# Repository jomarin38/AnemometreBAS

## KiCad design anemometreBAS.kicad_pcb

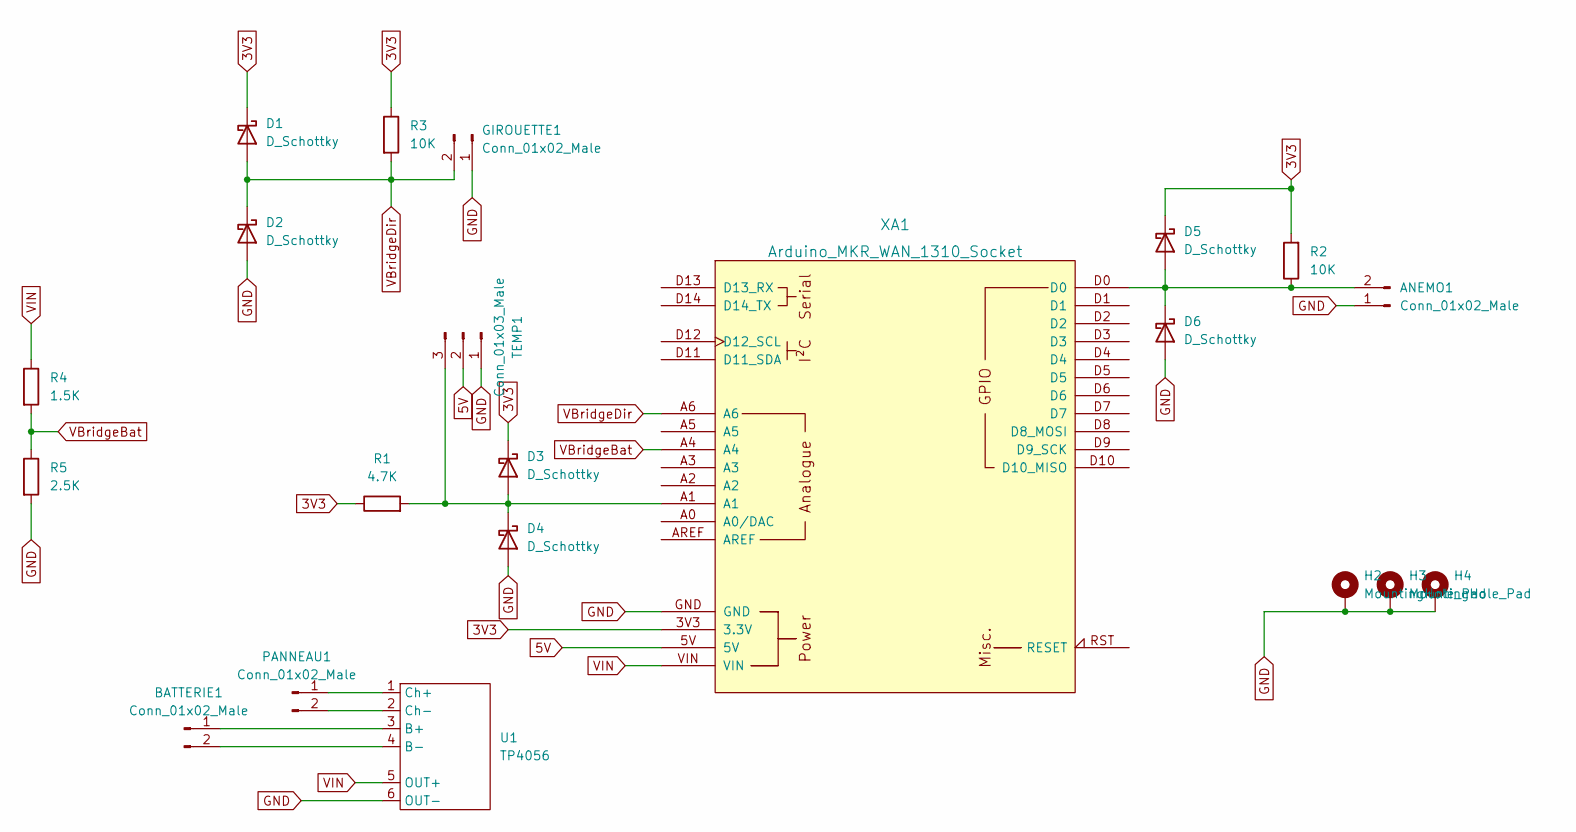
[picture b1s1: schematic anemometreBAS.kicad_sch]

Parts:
ANEMO1: Conn_01x02_Male; JST_XH_B3B-XH-A_1x03_P2.50mm_Vertical
BATTERIE1: Conn_01x02_Male; JST_XH_B2B-XH-A_1x02_P2.50mm_Vertical
D1, D2, D3, D4, D5, D6: D_Schottky; D_DO-35_SOD27_P7.62mm_Horizontal
GIROUETTE1: Conn_01x02_Male; JST_XH_B3B-XH-A_1x03_P2.50mm_Vertical
H2, H3, H4: MountingHole_Pad; MountingHole_3.2mm_M3_Pad_TopBottom
PANNEAU1: Conn_01x02_Male; JST_XH_B2B-XH-A_1x02_P2.50mm_Vertical
R1: 4.7K; R_Axial_DIN0204_L3.6mm_D1.6mm_P7.62mm_Horizontal
R2, R3: 10K; R_Axial_DIN0204_L3.6mm_D1.6mm_P7.62mm_Horizontal
R4: 1.5K; R_Axial_DIN0204_L3.6mm_D1.6mm_P7.62mm_Horizontal
R5: 2.5K; R_Axial_DIN0204_L3.6mm_D1.6mm_P7.62mm_Horizontal
TEMP1: Conn_01x03_Male; JST_XH_B3B-XH-A_1x03_P2.50mm_Vertical
U1: TP4056
XA1: Arduino_MKR_WAN_1310_Socket; Arduino_MKR_FOX_1200_Socket

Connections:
3V3: D1.1 (K), D3.1 (K), D5.1 (K), R1.1, R2.2, R3.1, XA1.3V3 (3.3V)
5V: TEMP1.2, XA1.5V
GND: ANEMO1.1, D2.2 (A), D4.2 (A), D6.2 (A), GIROUETTE1.1, H2.1, H3.1, H4.1, R5.2, TEMP1.1, U1.6 (OUT-), XA1.GND
unnamed: BATTERIE1.1, U1.3 (B+)
unnamed: BATTERIE1.2, U1.4 (B-)
unnamed: PANNEAU1.1, U1.1 (Ch+)
unnamed: PANNEAU1.2, U1.2 (Ch-)
unnamed: D3.2 (A), D4.1 (K), R1.2, TEMP1.3, XA1.A1
unnamed: ANEMO1.2, D5.2 (A), D6.1 (K), R2.1, XA1.D0
VBridgeBat: R4.2, R5.1, XA1.A4
VBridgeDir: D1.2 (A), D2.1 (K), GIROUETTE1.2, R3.2, XA1.A6
VIN: R4.1, U1.5 (OUT+), XA1.VIN

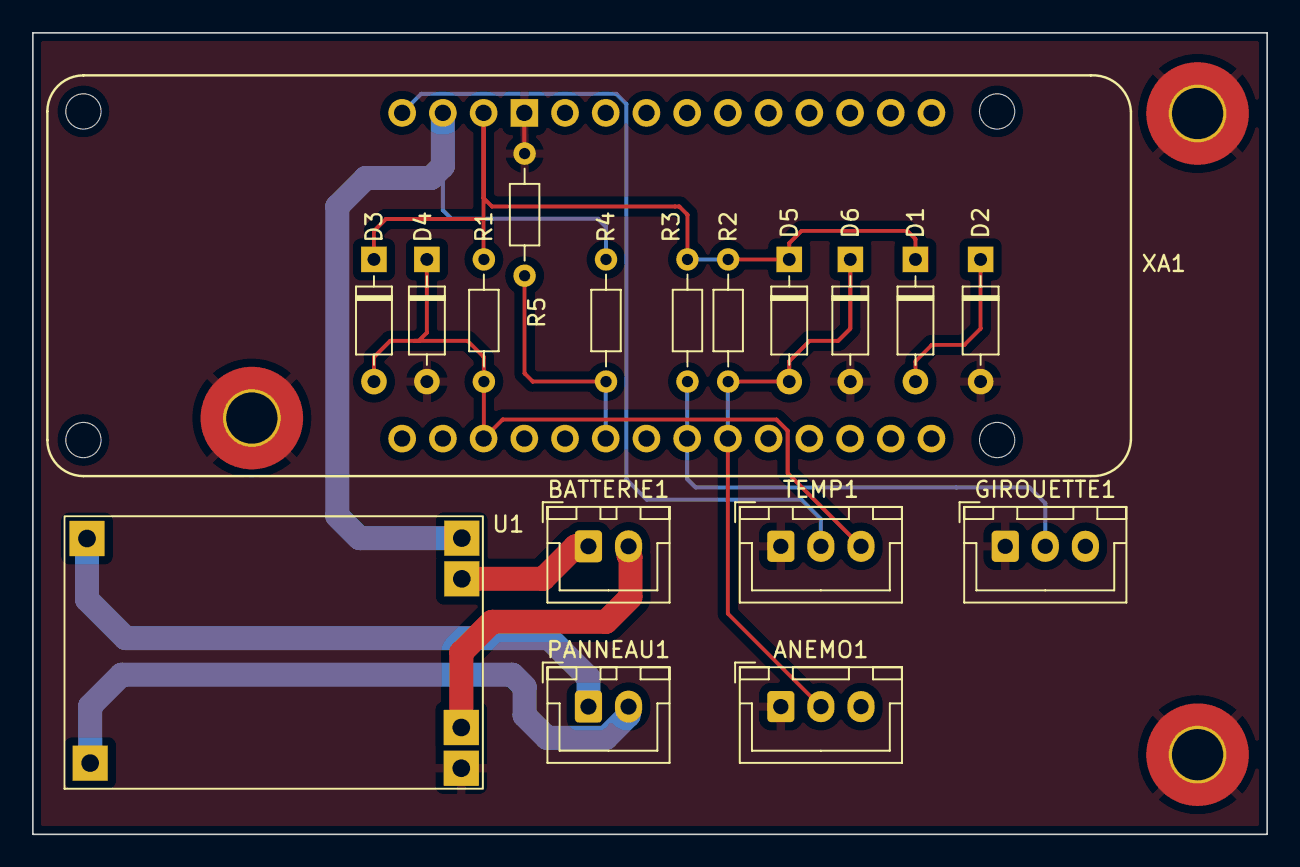
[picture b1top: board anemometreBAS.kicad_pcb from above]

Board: 2 copper layers, 77.0 x 50.0 mm, 21 parts (0 on the bottom side), 12 nets.

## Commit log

2023-01-08 Initial version
2023-01-11 fix error
2023-01-15 first pcb version with schematic footprint update
2023-01-19 schematic GND at the same pin for each connector add M3 hole*3 connected to GND PCB first routing
2023-01-20 Adding 3D model
2023-01-20 route temp sensor data change +5V net location change hole location drc ok only one error with hole under mkr processing board
2023-01-21 pcb without smd resistor first routing version
2023-01-28 change layer of solar panel and battery mngt card unshow $Reference and value
2023-01-28 change layer of solar panel and battery mngt card unshown $refence and value
2023-01-28 Adding pins socket connectors for MKR1310
2023-01-29 adding optionnal CEM schottky diode MKR 3D model update
2023-01-29 update 3D models with MKR pin shocket
2023-02-19 Pcb traversant (#1)
    * first pcb version with schematic footprint update
    * schematic
    GND at the same pin for each connector
    add M3 hole*3 connected to GND
    PCB
    first routing
2023-03-19 Fix power issue
2023-03-19 add power connector as jst routing pcb
2023-06-17 Corrections alim (#2)
    * Fix power issue
    * add power connector as jst
    routing pcb
    ---------
2023-06-17 Move PCB in subdirectory
2023-06-17 adding arduino code
2023-06-17 indicate where to enter APPEUI and APPKEY
